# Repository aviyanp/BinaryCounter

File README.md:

# BinaryCounter
basic thingy

This is a counter that goes from 0 to 2^4 - 1 (a.k.a. 0-15). If you press all buttons at once it should flash all LEDs as well.

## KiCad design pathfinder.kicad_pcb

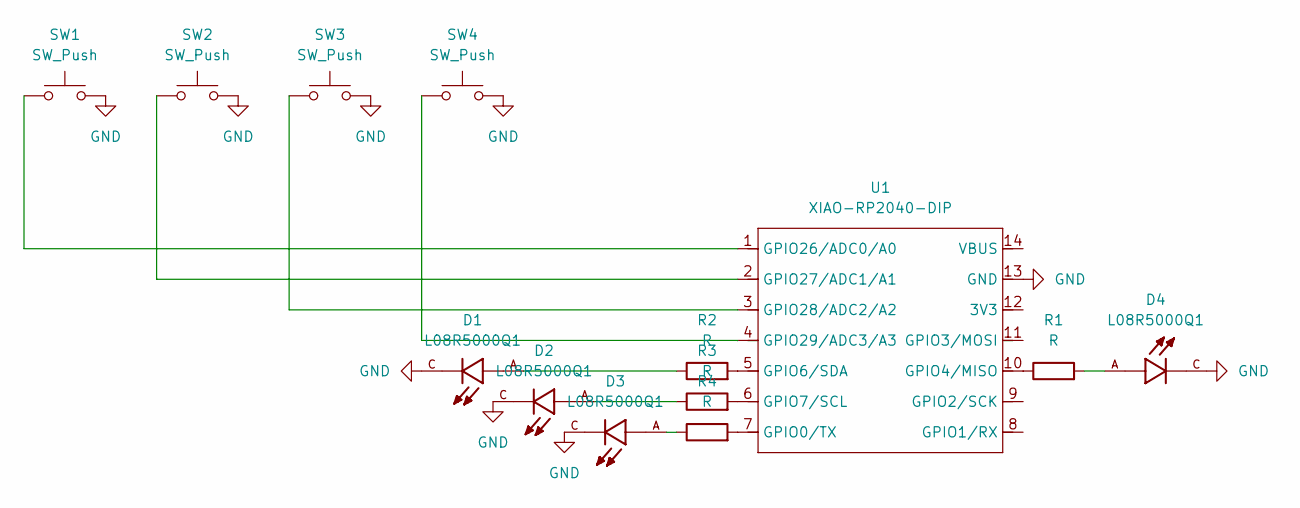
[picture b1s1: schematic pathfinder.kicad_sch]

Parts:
D1, D2, D3, D4: L08R5000Q1; LEDRD254W57D500H1070; PARTREV NA
R1, R2, R3, R4: R; R_Axial_DIN0204_L3.6mm_D1.6mm_P5.08mm_Horizontal
SW1, SW2, SW3, SW4: SW_Push; SW_Cherry_MX_1.00u_PCB
U1: XIAO-RP2040-DIP

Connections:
GND: D1.C, D2.C, D3.C, D4.C, SW1.2, SW2.2, SW3.2, SW4.2, U1.13 (GND)
unnamed: D1.A, R2.1
unnamed: D2.A, R3.1
unnamed: D3.A, R4.1
unnamed: D4.A, R1.2
unnamed: R4.2, U1.7 (GPIO0/TX)
unnamed: R1.1, U1.10 (GPIO4/MISO)
unnamed: R2.2, U1.5 (GPIO6/SDA)
unnamed: R3.2, U1.6 (GPIO7/SCL)
unnamed: SW1.1, U1.1 (GPIO26/ADC0/A0)
unnamed: SW2.1, U1.2 (GPIO27/ADC1/A1)
unnamed: SW3.1, U1.3 (GPIO28/ADC2/A2)
unnamed: SW4.1, U1.4 (GPIO29/ADC3/A3)

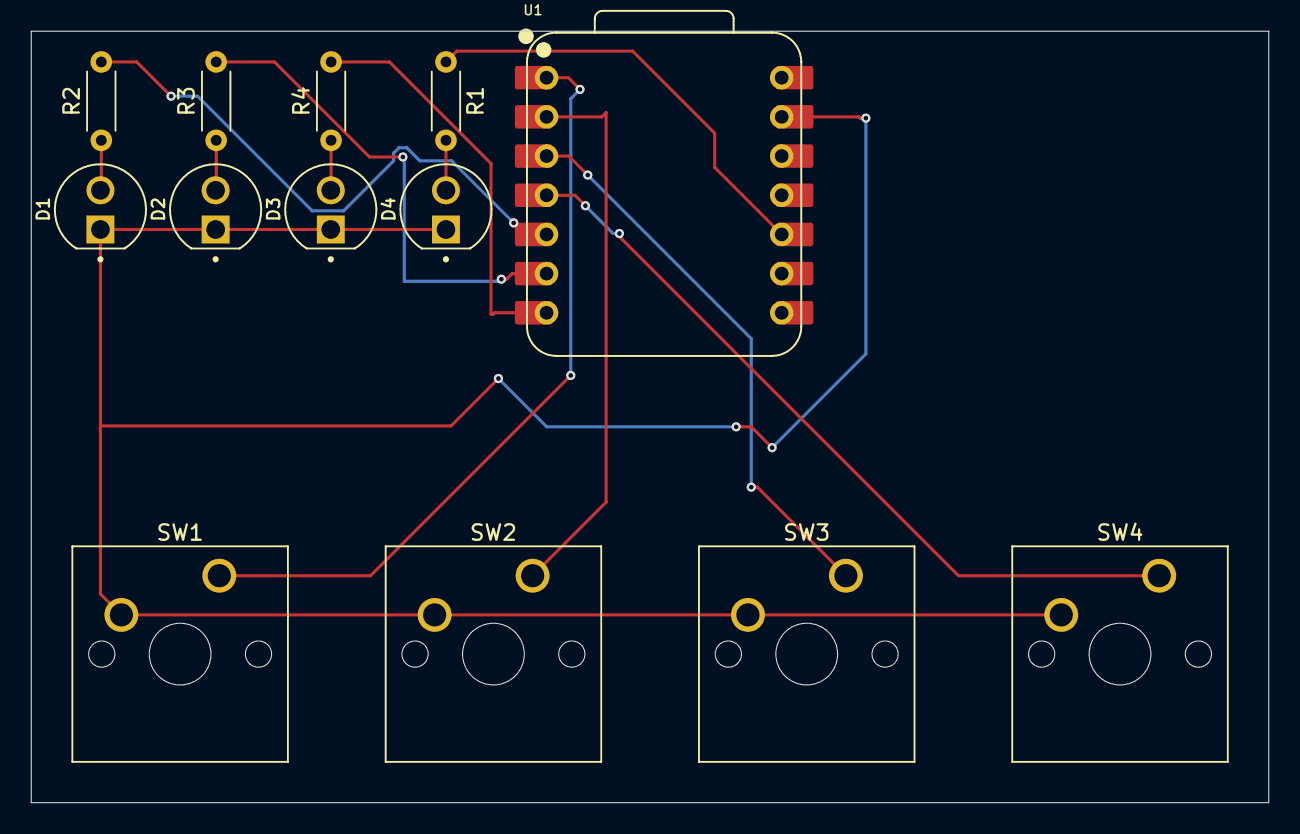
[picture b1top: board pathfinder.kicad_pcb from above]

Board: 2 copper layers, 80.2 x 50.0 mm, 13 parts (0 on the bottom side), 13 nets.

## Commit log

2025-07-03 gerber+other things
